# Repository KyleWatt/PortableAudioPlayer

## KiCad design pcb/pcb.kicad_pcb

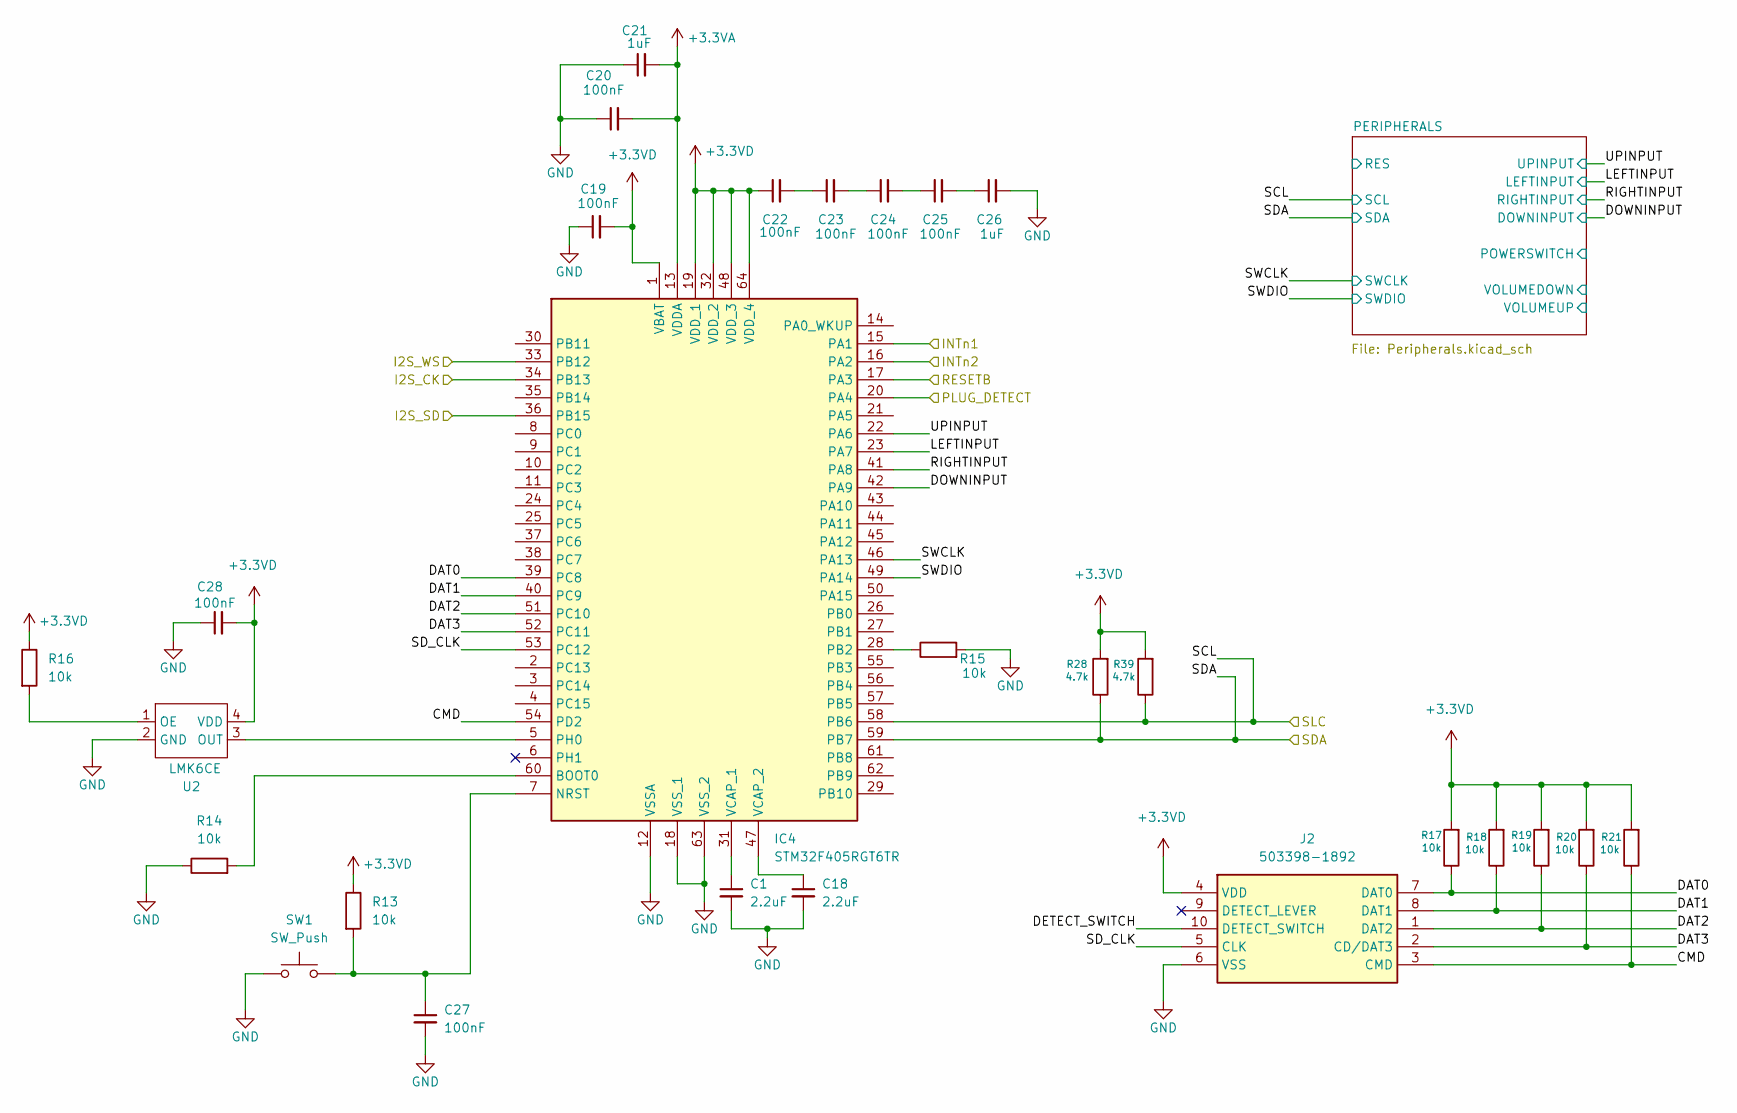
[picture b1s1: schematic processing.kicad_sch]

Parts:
C1, C18: 2.2uF; C_0805_2012Metric
C19, C20, C22, C23, C24, C25, C27, C28: 100nF; C_0805_2012Metric
C21, C26: 1uF; C_0805_2012Metric
IC4: STM32F405RGT6TR; QFP50P1200X1200X160-64N; Mouser Part Number 511-STM32F405RGT6TR
J2: 503398-1892; 5033981892; Mouser Part Number 538-503398-1892
R13, R14, R15, R16, R17, R18, R19, R20, R21: 10k; R_0805_2012Metric
R28, R39: 4.7k; R_0805_2012Metric
SW1: SW_Push; SW_Push_1P1T-MP_NO_Horizontal_Alps_SKRTLAE010
U2: LMK6CE; DLF0004A

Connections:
+3.3VA: C20.2, C21.2, IC4.13 (VDDA); also elsewhere on the board
+3.3VD: C19.2, C22.1, C28.2, IC4.1 (VBAT), IC4.19 (VDD_1), IC4.32 (VDD_2), IC4.48 (VDD_3), IC4.64 (VDD_4), J2.4 (VDD), R13.1, R16.1, R17.2, R18.2, R19.2, R20.2, R21.2, R28.2, R39.2, U2.4 (VDD); also elsewhere on the board
/AUDIO/I2S_CLK: IC4.34 (PB13); also elsewhere on the board
/AUDIO/I2S_SD: IC4.36 (PB15); also elsewhere on the board
/AUDIO/I2S_WS: IC4.33 (PB12); also elsewhere on the board
/AUDIO/PLUG_DETECT: IC4.20 (PA4); also elsewhere on the board
/AUDIO/RESETB: IC4.17 (PA3); also elsewhere on the board
/POWER/INTn1: IC4.15 (PA1); also elsewhere on the board
/POWER/INTn2: IC4.16 (PA2); also elsewhere on the board
/PROCESSING/CMD: IC4.54 (PD2), J2.3 (CMD), R21.1
/PROCESSING/DAT0: IC4.39 (PC8), J2.7 (DAT0), R17.1
/PROCESSING/DAT1: IC4.40 (PC9), J2.8 (DAT1), R18.1
/PROCESSING/DAT2: IC4.51 (PC10), J2.1 (DAT2), R19.1
/PROCESSING/DAT3: IC4.52 (PC11), J2.2 (CD/DAT3), R20.1
/PROCESSING/DETECT_SWITCH: J2.10 (DETECT_SWITCH)
/PROCESSING/DOWNINPUT: IC4.42 (PA9); also elsewhere on the board
/PROCESSING/LEFTINPUT: IC4.23 (PA7); also elsewhere on the board
/PROCESSING/RIGHTINPUT: IC4.41 (PA8); also elsewhere on the board
/PROCESSING/SCL: IC4.58 (PB6), R39.1; also elsewhere on the board
/PROCESSING/SDA: IC4.59 (PB7), R28.1; also elsewhere on the board
/PROCESSING/SD_CLK: IC4.53 (PC12), J2.5 (CLK)
/PROCESSING/SWCLK: IC4.46 (PA13); also elsewhere on the board
/PROCESSING/SWDIO: IC4.49 (PA14); also elsewhere on the board
/PROCESSING/UPINPUT: IC4.22 (PA6); also elsewhere on the board
GND: C1.2, C18.2, C19.1, C20.1, C21.1, C26.2, C27.2, C28.1, IC4.12 (VSSA), IC4.18 (VSS_1), IC4.63 (VSS_2), J2.6 (VSS), R14.1, R15.2, SW1.1, U2.2 (GND); also elsewhere on the board
unnamed: C22.2, C23.1
unnamed: C23.2, C24.1
unnamed: C24.2, C25.1
unnamed: C25.2, C26.1
unnamed: IC4.60 (BOOT0), R14.2
unnamed: C27.1, IC4.7 (NRST), R13.2, SW1.2
unnamed: IC4.28 (PB2), R15.1
unnamed: IC4.5 (PH0), U2.3 (OUT)
unnamed: C1.1, IC4.31 (VCAP_1)
unnamed: C18.1, IC4.47 (VCAP_2)
unnamed: R16.2, U2.1 (OE)

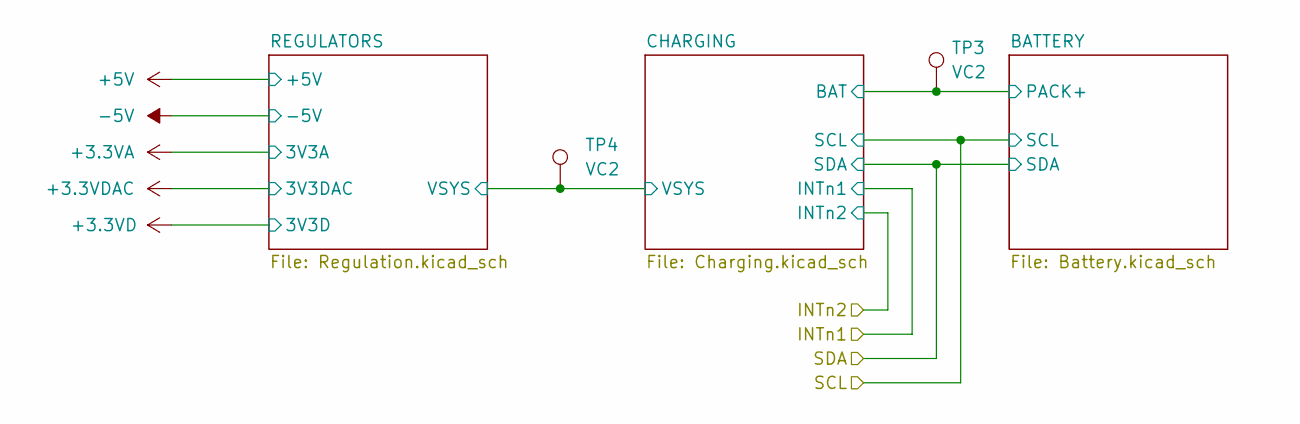
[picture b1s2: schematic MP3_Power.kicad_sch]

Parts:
TP3, TP4: VC2; TestPoint_Pad_3.0x3.0mm

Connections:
/POWER/BATTERY/PACK+: TP3.1; also elsewhere on the board
/POWER/CHARGING/VSYS: TP4.1; also elsewhere on the board

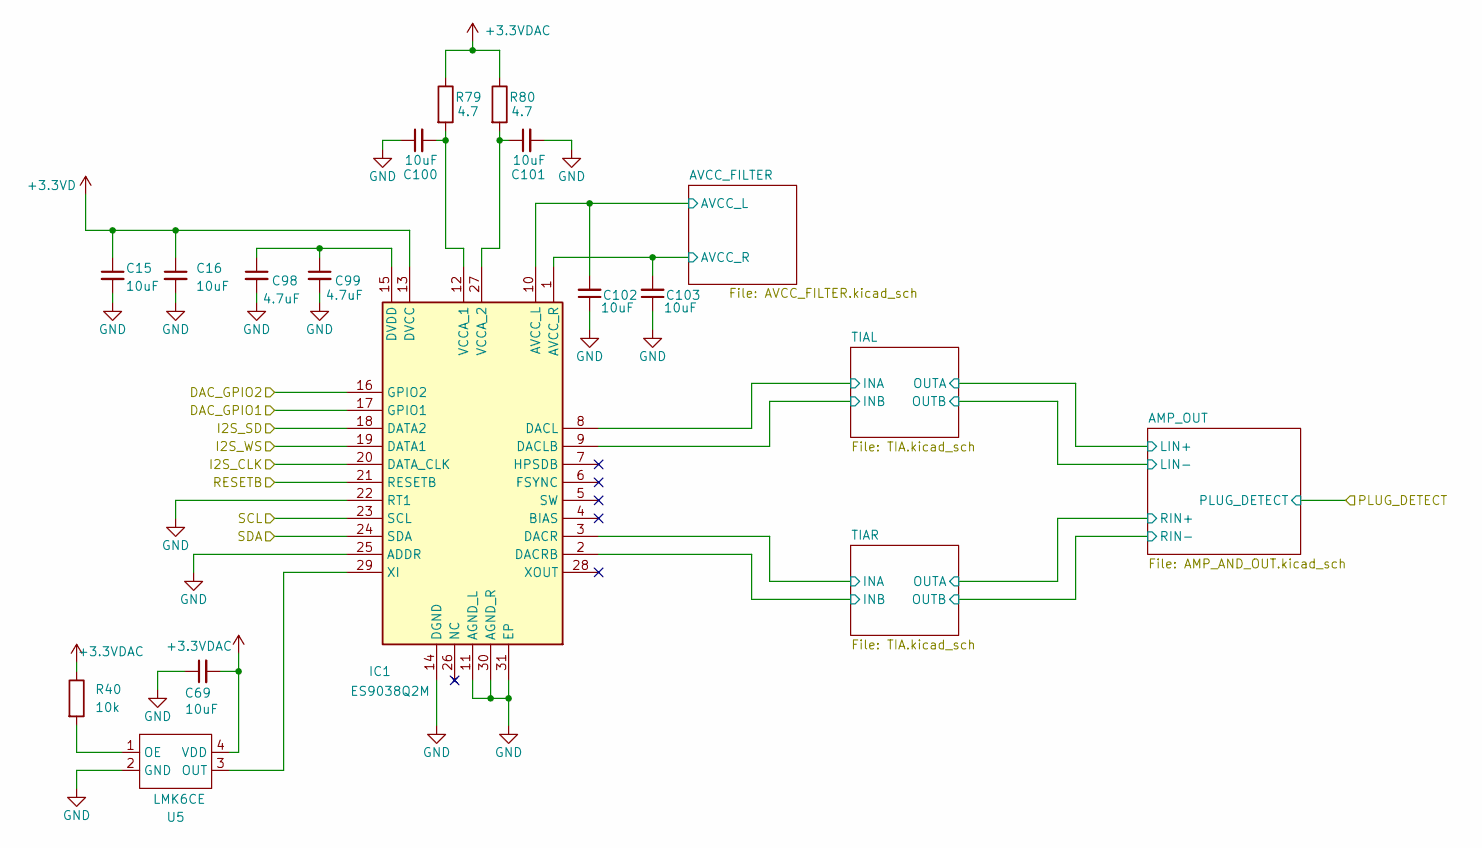
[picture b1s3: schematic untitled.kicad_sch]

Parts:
C15, C16, C69, C100, C101, C102, C103: 10uF; C_0805_2012Metric
C98, C99: 4.7uF; C_0805_2012Metric
IC1: ES9038Q2M; QFN40P300X500X80-31N-D; Mouser Part Number 460-ES9038Q2M
R40: 10k; R_0805_2012Metric
R79, R80: 4.7; R_0805_2012Metric
U5: LMK6CE; DLF0004A

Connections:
+3.3VD: C15.1, C16.1, IC1.13 (DVCC); also elsewhere on the board
+3.3VDAC: C69.2, R40.1, R79.1, R80.1, U5.4 (VDD); also elsewhere on the board
/AUDIO/AVCC_FILTER/AVCC_L: C102.2, IC1.10 (AVCC_L); also elsewhere on the board
/AUDIO/AVCC_FILTER/AVCC_R: C103.2, IC1.1 (AVCC_R); also elsewhere on the board
/AUDIO/DAC_GPIO1: IC1.17 (GPIO1)
/AUDIO/DAC_GPIO2: IC1.16 (GPIO2)
/AUDIO/I2S_CLK: IC1.20 (DATA_CLK); also elsewhere on the board
/AUDIO/I2S_SD: IC1.18 (DATA2); also elsewhere on the board
/AUDIO/I2S_WS: IC1.19 (DATA1); also elsewhere on the board
/AUDIO/RESETB: IC1.21 (RESETB); also elsewhere on the board
/AUDIO/TIAL/INA: IC1.8 (DACL); also elsewhere on the board
/AUDIO/TIAL/INB: IC1.9 (DACLB); also elsewhere on the board
/AUDIO/TIAR/INA: IC1.3 (DACR); also elsewhere on the board
/AUDIO/TIAR/INB: IC1.2 (DACRB); also elsewhere on the board
/PROCESSING/SCL: IC1.23 (SCL); also elsewhere on the board
/PROCESSING/SDA: IC1.24 (SDA); also elsewhere on the board
GND: C15.2, C16.2, C69.1, C98.2, C99.2, C100.1, C101.2, C102.1, C103.1, IC1.11 (AGND_L), IC1.14 (DGND), IC1.22 (RT1), IC1.25 (ADDR), IC1.30 (AGND_R), IC1.31 (EP), U5.2 (GND); also elsewhere on the board
unnamed: C98.1, C99.1, IC1.15 (DVDD)
unnamed: C100.2, IC1.12 (VCCA_1), R79.2
unnamed: C101.1, IC1.27 (VCCA_2), R80.2
unnamed: IC1.29 (XI), U5.3 (OUT)
unnamed: R40.2, U5.1 (OE)

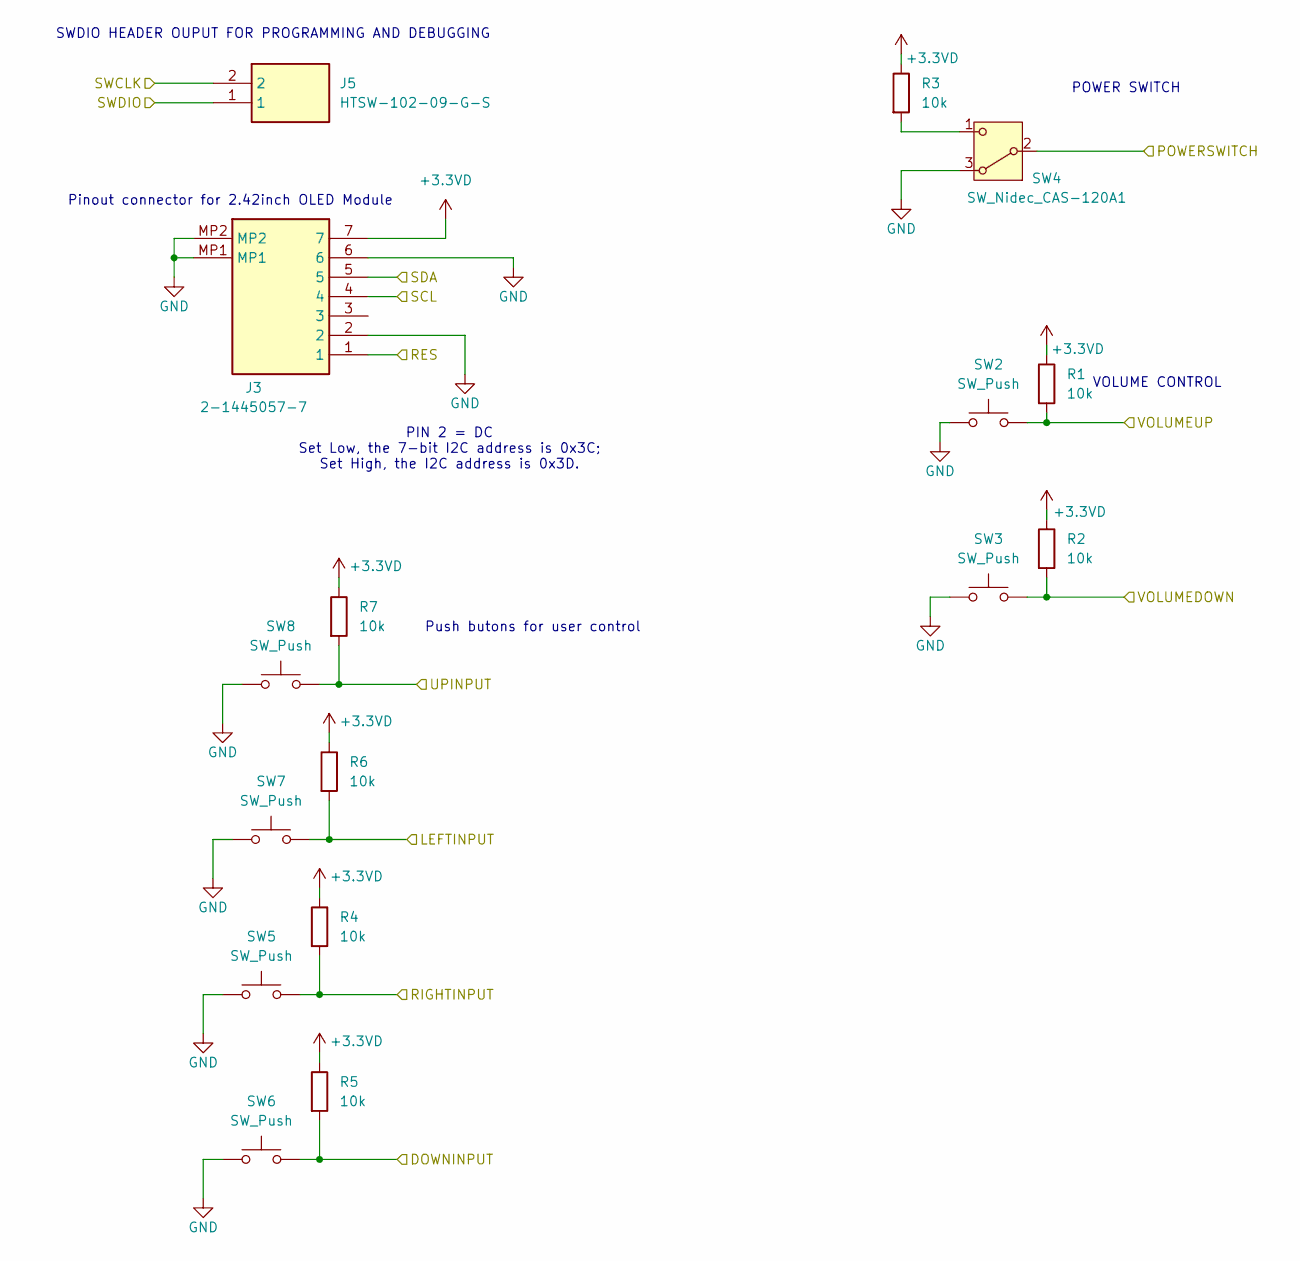
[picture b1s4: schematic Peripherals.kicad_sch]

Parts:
J3: 2-1445057-7; 214450577; Mouser Part Number 571-2-1445057-7
J5: HTSW-102-09-G-S; HTSW10209GS; Mouser Part Number 200-HTSW10209GS
R1, R2, R3, R4, R5, R6, R7: 10k; R_0805_2012Metric
SW2, SW3, SW5, SW6, SW7, SW8: SW_Push; SW_Push_1P1T-MP_NO_Horizontal_Alps_SKRTLAE010
SW4: SW_Nidec_CAS-120A1; Nidec_Copal_CAS-120A

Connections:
+3.3VD: J3.7, R1.1, R2.1, R3.1, R4.1, R5.1, R6.1, R7.1; also elsewhere on the board
/PROCESSING/DOWNINPUT: R5.2, SW6.2; also elsewhere on the board
/PROCESSING/LEFTINPUT: R6.2, SW7.2; also elsewhere on the board
/PROCESSING/PERIPHERALS/POWERSWITCH: SW4.2 (B)
/PROCESSING/PERIPHERALS/RES: J3.1
/PROCESSING/PERIPHERALS/VOLUMEDOWN: R2.2, SW3.2
/PROCESSING/PERIPHERALS/VOLUMEUP: R1.2, SW2.2
/PROCESSING/RIGHTINPUT: R4.2, SW5.2; also elsewhere on the board
/PROCESSING/SCL: J3.4; also elsewhere on the board
/PROCESSING/SDA: J3.5; also elsewhere on the board
/PROCESSING/SWCLK: J5.2; also elsewhere on the board
/PROCESSING/SWDIO: J5.1; also elsewhere on the board
/PROCESSING/UPINPUT: R7.2, SW8.2; also elsewhere on the board
GND: J3.2, J3.6, J3.MP1, J3.MP2, SW2.1, SW3.1, SW4.3 (A), SW5.1, SW6.1, SW7.1, SW8.1; also elsewhere on the board
unnamed: R3.2, SW4.1 (C)

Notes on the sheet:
PIN 2 = DC Set Low, the 7-bit I2C address is 0x3C; Set High, the I2C address is 0x3D.
Pinout connector for 2.42inch OLED Module
SWDIO HEADER OUPUT FOR PROGRAMMING AND DEBUGGING
Push butons for user control
POWER SWITCH
VOLUME CONTROL

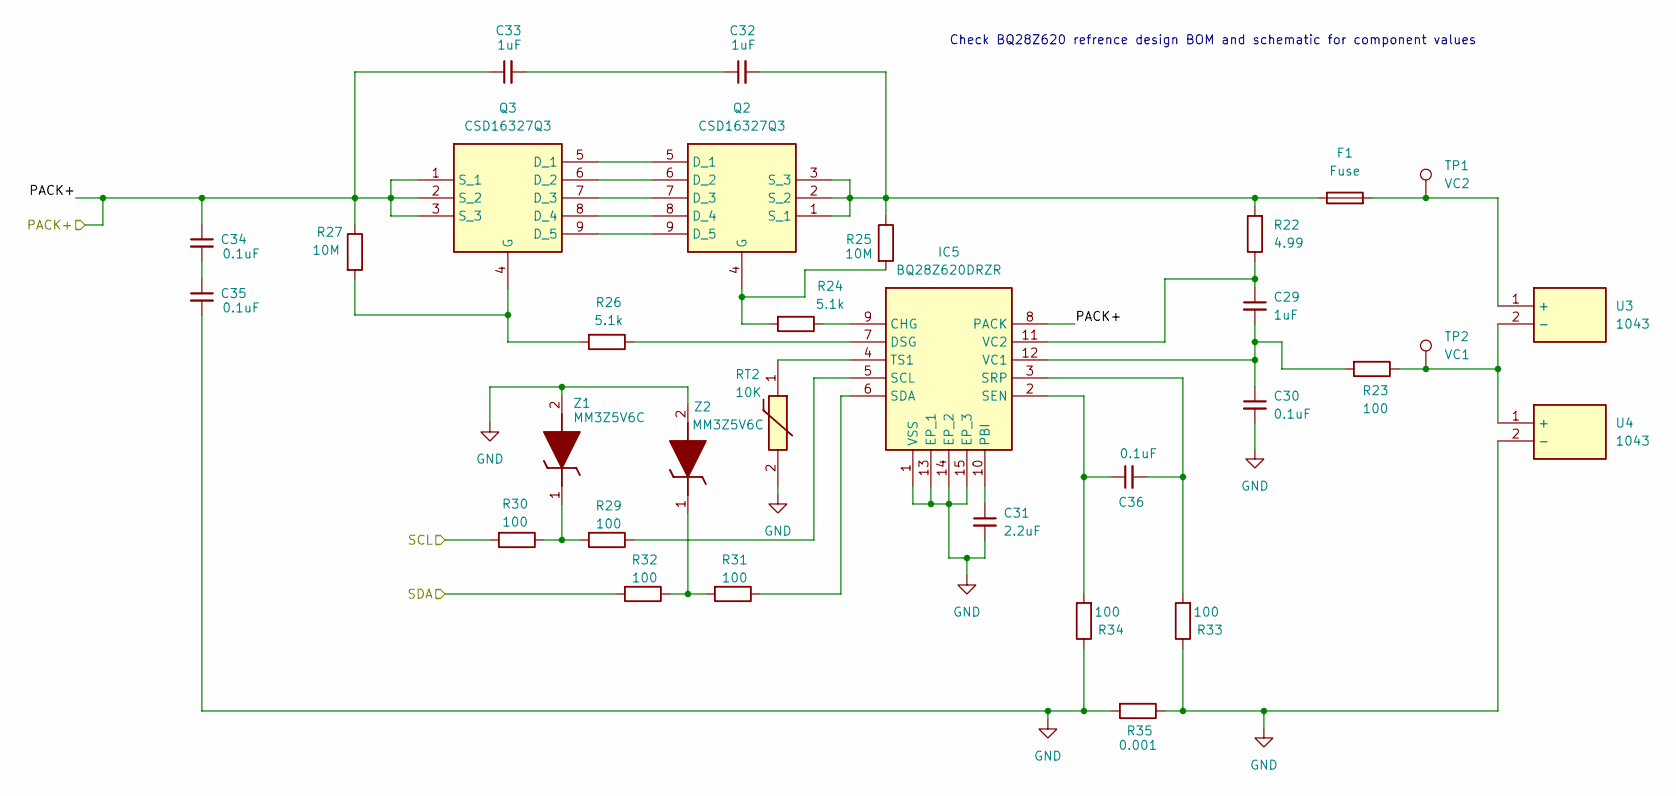
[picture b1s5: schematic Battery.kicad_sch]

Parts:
C29, C32, C33: 1uF; C_0805_2012Metric
C30, C34, C35, C36: 0.1uF; C_0805_2012Metric
C31: 2.2uF; C_0805_2012Metric
F1: Fuse; Fuse_0805_2012Metric
IC5: BQ28Z620DRZR; BQ28Z610DRZT; Mouser Part Number 595-BQ28Z620DRZR
Q2, Q3: CSD16327Q3; Mouser Part Number 595-CSD16327Q3
R22: 4.99; R_0805_2012Metric
R23, R29, R30, R31, R32, R33, R34: 100; R_0805_2012Metric
R24, R26: 5.1k; R_0805_2012Metric
R25, R27: 10M; R_0805_2012Metric
R35: 0.001; R_0805_2012Metric
RT2: 10K; 103AT2; Mouser Part Number 954-103AT-2
TP1: VC2; TestPoint_Pad_3.0x3.0mm
TP2: VC1; TestPoint_Pad_3.0x3.0mm
U3, U4: 1043; 1049; Mouser Part Number 534-1043
Z1, Z2: MM3Z5V6C; SODFL2513X100N; Mouser Part Number 512-MM3Z5V6C

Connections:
/POWER/BATTERY/PACK+: C33.1, C34.1, IC5.8 (PACK), Q3.1 (S_1), Q3.2 (S_2), Q3.3 (S_3), R27.1; also elsewhere on the board
/PROCESSING/SCL: R30.2; also elsewhere on the board
/PROCESSING/SDA: R32.2; also elsewhere on the board
GND: C30.2, C31.2, C35.2, IC5.1 (VSS), IC5.13 (EP_1), IC5.14 (EP_2), IC5.15 (EP_3), R33.1, R34.1, R35.1, R35.2, RT2.2, U4.2 (-), Z1.2 (A), Z2.2 (A); also elsewhere on the board
unnamed: C32.1, C33.2
unnamed: C34.2, C35.1
unnamed: IC5.9 (CHG), R24.1
unnamed: IC5.7 (DSG), R26.1
unnamed: C31.1, IC5.10 (PBI)
unnamed: IC5.5 (SCL), R29.1
unnamed: IC5.6 (SDA), R31.1
unnamed: C36.1, IC5.2 (SEN), R34.2
unnamed: C36.2, IC5.3 (SRP), R33.2
unnamed 85: IC5.4 (TS1), RT2.1; also elsewhere on the board
unnamed: C29.2, C30.1, IC5.12 (VC1), R23.2
unnamed: C29.1, IC5.11 (VC2), R22.1
unnamed: Q2.5 (D_1), Q3.5 (D_1)
unnamed: Q2.6 (D_2), Q3.6 (D_2)
unnamed: Q2.7 (D_3), Q3.7 (D_3)
unnamed: Q2.8 (D_4), Q3.8 (D_4)
unnamed: Q2.9 (D_5), Q3.9 (D_5)
unnamed: Q2.4 (G), R24.2, R25.2
unnamed: C32.2, F1.1, Q2.1 (S_1), Q2.2 (S_2), Q2.3 (S_3), R22.2, R25.1
unnamed: Q3.4 (G), R26.2, R27.2
unnamed: F1.2, TP1.1, U3.1 (+)
unnamed: R23.1, TP2.1, U3.2 (-), U4.1 (+)
unnamed: R29.2, R30.1, Z1.1 (K)
unnamed: R31.2, R32.1, Z2.1 (K)

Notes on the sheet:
Check BQ28Z620 refrence design BOM and schematic for component values

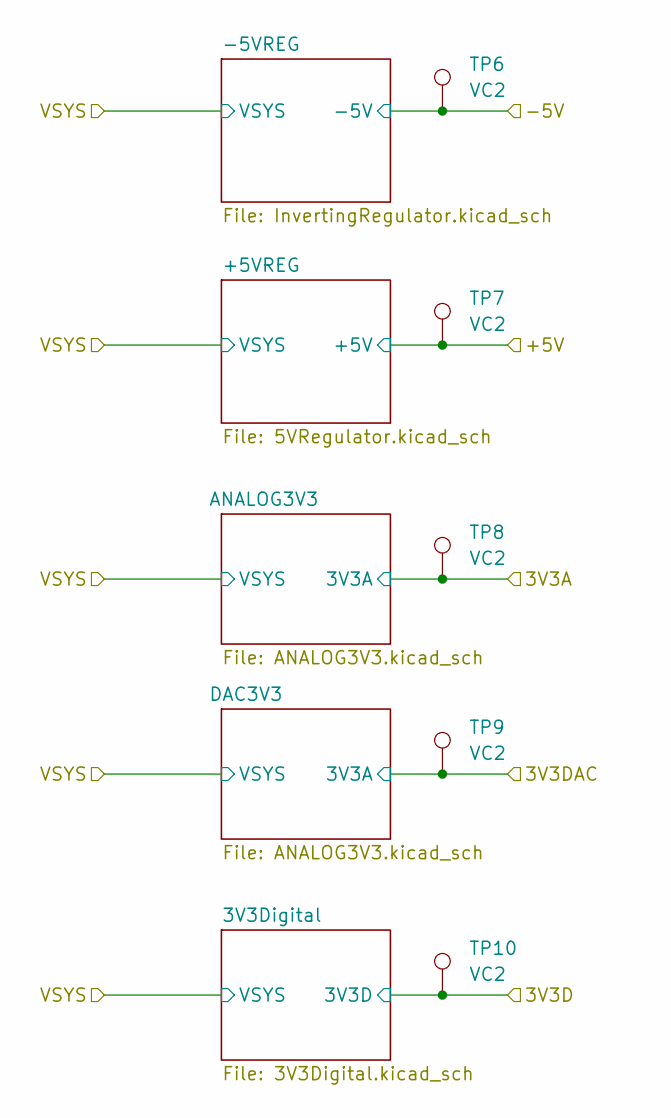
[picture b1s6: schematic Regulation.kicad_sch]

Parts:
TP6, TP7, TP8, TP9, TP10: VC2; TestPoint_Pad_3.0x3.0mm

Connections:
+3.3VA: TP8.1; also elsewhere on the board
+3.3VD: TP10.1; also elsewhere on the board
+3.3VDAC: TP9.1; also elsewhere on the board
+5V: TP7.1; also elsewhere on the board
-5V: TP6.1; also elsewhere on the board

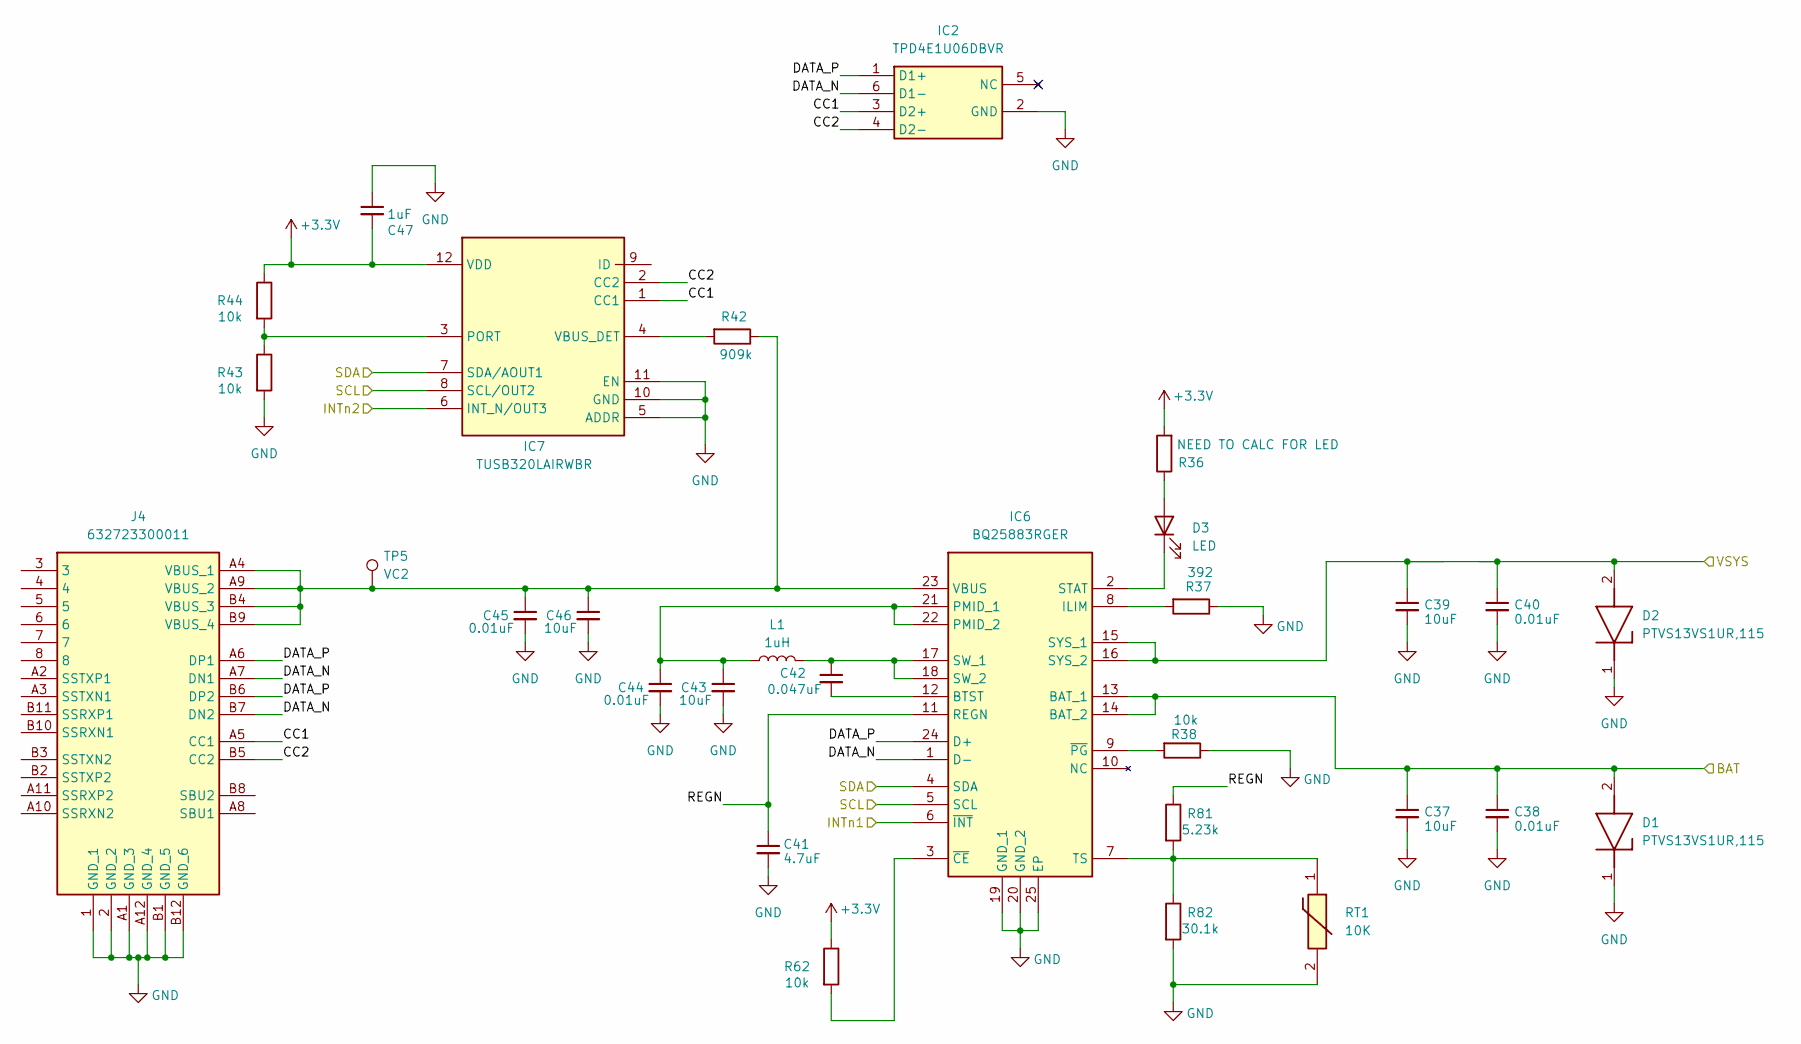
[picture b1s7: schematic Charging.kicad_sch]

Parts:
C37, C39, C43, C46: 10uF; C_0805_2012Metric
C38, C40, C44, C45: 0.01uF; C_0805_2012Metric
C41: 4.7uF; C_0805_2012Metric
C42: 0.047uF; C_0805_2012Metric
C47: 1uF; C_0805_2012Metric
D1, D2: PTVS13VS1UR,115; SOD123W; Mouser Part Number 771-PTVS13VS1UR115
D3: LED; LED_0805_2012Metric
IC2: TPD4E1U06DBVR; SOT95P280X145-6N; Mouser Part Number 595-TPD4E1U06DBVR
IC6: BQ25883RGER; QFN50P400X400X100-25N-D; Mouser Part Number 595-BQ25883RGER
IC7: TUSB320LAIRWBR; RWB0012A; Mouser Part Number 595-TUSB320LAIRWBR
J4: 632723300011; Mouser Part Number 710-632723300011
L1: 1uH; L_0805_2012Metric
R36: NEED TO CALC FOR LED; R_0805_2012Metric
R37: 392; R_0805_2012Metric
R38, R43, R44, R62: 10k; R_0805_2012Metric
R42: 909k; R_0805_2012Metric
R81: 5.23k; R_0805_2012Metric
R82: 30.1k; R_0805_2012Metric
RT1: 10K; 103AT2; Mouser Part Number 954-103AT-2
TP5: VC2; TestPoint_Pad_3.0x3.0mm

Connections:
+3.3V: C47.2, IC7.12 (VDD), R36.2, R44.1, R62.1
/POWER/BATTERY/PACK+: C37.1, C38.1, D1.2 (A), IC6.13 (BAT_1), IC6.14 (BAT_2); also elsewhere on the board
/POWER/CHARGING/CC1: IC2.3 (D2+), IC7.1 (CC1), J4.A5 (CC1)
/POWER/CHARGING/CC2: IC2.4 (D2-), IC7.2 (CC2), J4.B5 (CC2)
/POWER/CHARGING/DATA_N: IC2.6 (D1-), IC6.1 (D-), J4.A7 (DN1), J4.B7 (DN2)
/POWER/CHARGING/DATA_P: IC2.1 (D1+), IC6.24 (D+), J4.A6 (DP1), J4.B6 (DP2)
/POWER/CHARGING/REGN: C41.1, IC6.11 (REGN), R81.1
/POWER/CHARGING/VSYS: C39.1, C40.1, D2.2 (A), IC6.15 (SYS_1), IC6.16 (SYS_2); also elsewhere on the board
/POWER/INTn1: IC6.6 (~INT); also elsewhere on the board
/POWER/INTn2: IC7.6 (INT_N/OUT3); also elsewhere on the board
/PROCESSING/SCL: IC6.5 (SCL), IC7.8 (SCL/OUT2); also elsewhere on the board
/PROCESSING/SDA: IC6.4 (SDA), IC7.7 (SDA/AOUT1); also elsewhere on the board
GND: C37.2, C38.2, C39.2, C40.2, C41.2, C43.2, C44.2, C45.2, C46.2, C47.1, D1.1 (K), D2.1 (K), IC2.2 (GND), IC6.19 (GND_1), IC6.20 (GND_2), IC6.25 (EP), IC7.5 (ADDR), IC7.10 (GND), IC7.11 (EN), J4.1 (GND_1), J4.2 (GND_2), J4.A1 (GND_3), J4.A12 (GND_4), J4.B1 (GND_5), J4.B12 (GND_6), R37.1, R38.1, R43.2, R82.2, RT1.2; also elsewhere on the board
unnamed: D3.2 (A), R36.1
unnamed: D3.1 (K), IC6.2 (STAT)
unnamed: C42.2, IC6.12 (BTST)
unnamed: IC6.8 (ILIM), R37.2
unnamed: C43.1, C44.1, IC6.21 (PMID_1), IC6.22 (PMID_2), L1.1
unnamed: C42.1, IC6.17 (SW_1), IC6.18 (SW_2), L1.2
unnamed: IC6.7 (TS), R81.2, R82.1, RT1.1
unnamed: C45.1, C46.1, IC6.23 (VBUS), J4.A4 (VBUS_1), J4.A9 (VBUS_2), J4.B4 (VBUS_3), J4.B9 (VBUS_4), R42.1, TP5.1
unnamed: IC6.3 (~CE), R62.2
unnamed: IC6.9 (~PG), R38.2
unnamed: IC7.3 (PORT), R43.1, R44.2
unnamed: IC7.4 (VBUS_DET), R42.2

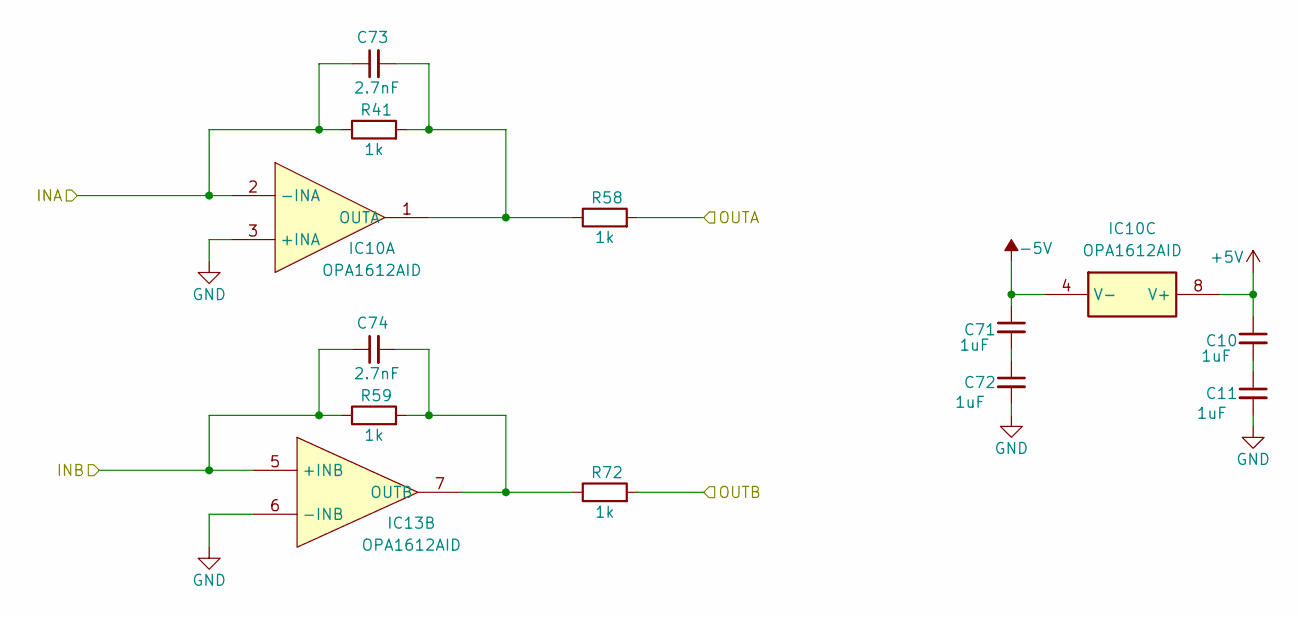
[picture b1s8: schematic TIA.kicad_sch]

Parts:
C10, C11, C71, C72: 1uF; C_0805_2012Metric
C73, C74: 2.7nF; C_0805_2012Metric
IC10, IC13: OPA1612AID; SOIC127P600X175-8N; Mouser Part Number 595-OPA1612AID
R41, R58, R59, R72: 1k; R_0805_2012Metric

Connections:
+5V: C10.1, IC10.8 (V+); also elsewhere on the board
-5V: C71.1, IC10.4 (V-); also elsewhere on the board
/AUDIO/AMP_OUT/LIN+: R58.2; also elsewhere on the board
/AUDIO/AMP_OUT/LIN-: R72.2; also elsewhere on the board
/AUDIO/TIAL/INA: C73.1, IC10.2 (-INA), R41.1; also elsewhere on the board
/AUDIO/TIAL/INB: C74.1, IC13.5 (+INB), R59.1; also elsewhere on the board
GND: C11.2, C72.2, IC10.3 (+INA), IC13.6 (-INB); also elsewhere on the board
unnamed: C10.2, C11.1
unnamed: C71.2, C72.1
unnamed: C73.2, IC10.1 (OUTA), R41.2, R58.1
unnamed: C74.2, IC13.7 (OUTB), R59.2, R72.1

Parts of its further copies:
C75, C76: 2.7nF; C_0805_2012Metric
C77, C78, C79, C80: 1uF; C_0805_2012Metric
IC11, IC14: OPA1612AID; SOIC127P600X175-8N; Mouser Part Number 595-OPA1612AID
R61, R63, R65, R73: 1k; R_0805_2012Metric

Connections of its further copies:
+5V: C77.1, IC11.8 (V+); also elsewhere on the board
-5V: C79.1, IC11.4 (V-); also elsewhere on the board
/AUDIO/AMP_OUT/RIN+: R65.2; also elsewhere on the board
/AUDIO/AMP_OUT/RIN-: R73.2; also elsewhere on the board
/AUDIO/TIAR/INA: C75.1, IC11.2 (-INA), R61.1; also elsewhere on the board
/AUDIO/TIAR/INB: C76.1, IC14.5 (+INB), R63.1; also elsewhere on the board
GND: C78.2, C80.2, IC11.3 (+INA), IC14.6 (-INB); also elsewhere on the board
unnamed: C77.2, C78.1
unnamed: C79.2, C80.1
unnamed: C75.2, IC11.1 (OUTA), R61.2, R65.1
unnamed: C76.2, IC14.7 (OUTB), R63.2, R73.1

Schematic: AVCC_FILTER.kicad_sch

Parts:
C14, C17, C87, C88: 1uF; C_0805_2012Metric
C70, C90: 47uF; C_0805_2012Metric
C85, C86, C89, C91: 10uF; C_0805_2012Metric
IC13, IC15: OPA1612AID; SOIC127P600X175-8N; Mouser Part Number 595-OPA1612AID
R60, R64: 22; R_0805_2012Metric

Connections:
+3.3VA: C85.2, C89.2, R60.1, R64.1; also elsewhere on the board
+5V: C14.1, IC13.8 (V+); also elsewhere on the board
-5V: C87.1, IC13.4 (V-); also elsewhere on the board
/AUDIO/AVCC_FILTER/AVCC_L: C91.2, IC15.7 (OUTB); also elsewhere on the board
/AUDIO/AVCC_FILTER/AVCC_R: C86.2, IC13.1 (OUTA); also elsewhere on the board
GND: C17.2, C70.1, C85.1, C86.1, C88.2, C89.1, C90.1, C91.1, IC13.3 (+INA), IC15.6 (-INB); also elsewhere on the board
unnamed: C14.2, C17.1
unnamed: C87.2, C88.1
unnamed: C70.2, IC13.2 (-INA), R60.2
unnamed: C90.2, IC15.5 (+INB), R64.2

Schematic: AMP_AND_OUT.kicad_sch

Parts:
C81, C82, C83, C84: 1uF; C_0805_2012Metric
IC3: TPA6120A2DWPR; SOIC127P1040X275-21N; Mouser Part Number 595-TPA6120A2DWPR
J1: SJ3-35083C-TR; SJ335083CTR; Mouser Part Number 179-SJ3-35083C-TR
R66, R67, R68, R69: 1k; R_0805_2012Metric
R70, R71: 39.2; R_0805_2012Metric

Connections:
+5V: C83.1, C84.1, IC3.3 (LVCC+), IC3.18 (RVCC+); also elsewhere on the board
-5V: C81.1, C82.1, IC3.1 (LVCC-), IC3.20 (RVCC-); also elsewhere on the board
/AUDIO/AMP_OUT/LIN+: IC3.4 (LIN+), R66.2; also elsewhere on the board
/AUDIO/AMP_OUT/LIN-: IC3.5 (LIN-), R69.1; also elsewhere on the board
/AUDIO/AMP_OUT/RIN+: IC3.17 (RIN+), R67.2; also elsewhere on the board
/AUDIO/AMP_OUT/RIN-: IC3.16 (RIN-), R68.1; also elsewhere on the board
/AUDIO/PLUG_DETECT: J1.4 (RING_SWITCH); also elsewhere on the board
GND: C81.2, C82.2, C83.2, C84.2, IC3.6 (NC_1), IC3.7 (NC_2), IC3.8 (NC_3), IC3.9 (NC_4), IC3.10 (NC_5), IC3.11 (NC_6), IC3.12 (NC_7), IC3.13 (NC_8), IC3.14 (NC_9), IC3.15 (NC_10), IC3.21 (EP), J1.1 (SLEEVE), R66.1, R67.1; also elsewhere on the board
unnamed: IC3.2 (LOUT), R69.2, R71.1
unnamed: IC3.19 (ROUT), R68.2, R70.1
unnamed: J1.5 (RING), R70.2
unnamed: J1.2 (TIP), R71.2

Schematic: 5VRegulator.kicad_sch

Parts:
C51: 10uF; C_0805_2012Metric
C52, C53, C54: 1uF; C_0805_2012Metric
C56: 22uF; C_0805_2012Metric
C57, C58: 4.7uF; C_0805_2012Metric
IC17: LT3045EMSE#PBF; SOP65P490X110-13N; Mouser Part Number 584-LT3045EMSE#PBF
R48: 52.3k; R_0805_2012Metric
R49: 750k; R_0805_2012Metric
R50: 49.9k; R_0805_2012Metric
R51: 200k; R_0805_2012Metric
R52: 249; R_0805_2012Metric

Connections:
+5V: IC17.11 (OUT_1), IC17.12 (OUT_2), R49.1; also elsewhere on the board
/POWER/CHARGING/VSYS: C51.1, C52.1, C53.1, C54.1, IC17.1 (IN_1), IC17.2 (IN_2), IC17.3 (IN_3), IC17.4 (EN/UV), R51.2; also elsewhere on the board
GND: C51.2, C52.2, C53.2, C54.2, C56.2, C57.1, C58.1, IC17.9 (GND_1), IC17.13 (GND_2), R48.1, R50.2, R52.2; also elsewhere on the board
unnamed: IC17.6 (ILIM), R52.1
unnamed: C57.2, IC17.10 (OUTS)
unnamed: IC17.5 (PG), R51.1
unnamed: C58.2, IC17.7 (PGFB), R49.2, R50.1
unnamed: C56.1, IC17.8 (SET), R48.2

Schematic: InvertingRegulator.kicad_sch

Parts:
C48, C49, C50: 4.7uF; C_0805_2012Metric
IC8: LM27761DSGT; SON50P200X200X80-9N; Mouser Part Number 595-LM27761DSGT
R45: 10k; R_0805_2012Metric
R46: 301k; R_0805_2012Metric
R47: 100k; R_0805_2012Metric

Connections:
-5V: IC8.4 (VOUT), R46.1; also elsewhere on the board
/POWER/CHARGING/VSYS: C50.1, IC8.1 (VIN), R45.2; also elsewhere on the board
GND: C48.1, C50.2, IC8.2 (GND), IC8.9 (EP), R47.2; also elsewhere on the board
unnamed: C49.1, IC8.8 (C1+)
unnamed: C49.2, IC8.7 (C1-)
unnamed: C48.2, IC8.3 (CPOUT)
unnamed: IC8.6 (EN), R45.1
unnamed: IC8.5 (VFB), R46.2, R47.1

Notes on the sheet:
VOUT =–1.22 V × (R1 + R2) / R2
R1/R2 = 3.098 => Vout = -5V

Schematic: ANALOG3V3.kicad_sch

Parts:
C55: 10uF; C_0805_2012Metric
C59, C60, C61: 1uF; C_0805_2012Metric
C62, C64: 4.7uF; C_0805_2012Metric
C63: 22uF; C_0805_2012Metric
IC12: LT3045EMSE#PBF; SOP65P490X110-13N; Mouser Part Number 584-LT3045EMSE#PBF
R53: 200k; R_0805_2012Metric
R54: 249; R_0805_2012Metric
R55: 31.6k; R_0805_2012Metric
R56: 453k; R_0805_2012Metric
R57: 49.9k; R_0805_2012Metric

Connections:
+3.3VA: IC12.11 (OUT_1), IC12.12 (OUT_2), R56.1; also elsewhere on the board
/POWER/CHARGING/VSYS: C55.1, C59.1, C60.1, C61.1, IC12.1 (IN_1), IC12.2 (IN_2), IC12.3 (IN_3), IC12.4 (EN/UV), R53.2; also elsewhere on the board
GND: C55.2, C59.2, C60.2, C61.2, C62.1, C63.2, C64.1, IC12.9 (GND_1), IC12.13 (GND_2), R54.2, R55.1, R57.2; also elsewhere on the board
unnamed: IC12.6 (ILIM), R54.1
unnamed: C62.2, IC12.10 (OUTS)
unnamed: IC12.5 (PG), R53.1
unnamed: C64.2, IC12.7 (PGFB), R56.2, R57.1
unnamed: C63.1, IC12.8 (SET), R55.2

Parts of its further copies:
C68: 10uF; C_0805_2012Metric
C92, C93, C94: 1uF; C_0805_2012Metric
C95, C97: 4.7uF; C_0805_2012Metric
C96: 22uF; C_0805_2012Metric
IC16: LT3045EMSE#PBF; SOP65P490X110-13N; Mouser Part Number 584-LT3045EMSE#PBF
R74: 200k; R_0805_2012Metric
R75: 249; R_0805_2012Metric
R76: 31.6k; R_0805_2012Metric
R77: 453k; R_0805_2012Metric
R78: 49.9k; R_0805_2012Metric

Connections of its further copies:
+3.3VDAC: IC16.11 (OUT_1), IC16.12 (OUT_2), R77.1; also elsewhere on the board
/POWER/CHARGING/VSYS: C68.1, C92.1, C93.1, C94.1, IC16.1 (IN_1), IC16.2 (IN_2), IC16.3 (IN_3), IC16.4 (EN/UV), R74.2; also elsewhere on the board
GND: C68.2, C92.2, C93.2, C94.2, C95.1, C96.2, C97.1, IC16.9 (GND_1), IC16.13 (GND_2), R75.2, R76.1, R78.2; also elsewhere on the board
unnamed: IC16.6 (ILIM), R75.1
unnamed: C95.2, IC16.10 (OUTS)
unnamed: IC16.5 (PG), R74.1
unnamed: C97.2, IC16.7 (PGFB), R77.2, R78.1
unnamed: C96.1, IC16.8 (SET), R76.2

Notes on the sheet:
During power-up, VOUT gradually ramps from 0V to 5V over 10-50ms, not instantly. The LT3045 uses the PGFB pin to detect whether it's starting up or already running. When VOUT is low (making PGFB < 300mV), the IC recognizes it's in start-up mode and pumps 2mA into the SET pin to quickly charge the l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
V_PGFB = VOUT × RPG1 / (RPG1 + RPG2) When V_PGFB < 0.3V FAST STARTUP ENGAGES When V_PGFB > 0.3V FAST STARTUP DISENGAGES VOUT(threshold) = 0.3V × (RPG1 + RPG2) / RPG1 VOUT(threshold) = 0.3V × (1 + RPG2/RPG1)
5V = 0.8V × (1 + R_SET/10kΩ) 5/0.8 = 1 + R_SET/10kΩ 6.25 = 1 + R_SET/10kΩ R_SET = 52.5kΩ

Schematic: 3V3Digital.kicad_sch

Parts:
C65, C66: 2.2uF; C_0805_2012Metric
C67: 1uF; C_0805_2012Metric
IC9: ADPL42002ARDZ-3.3-R7; SOIC127P600X175-9N; Manufacturer_Part_Number ADPL42002ARDZ-3.3-R7

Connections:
+3.3VD: C66.1, IC9.1 (VOUT_1), IC9.2 (VOUT_2), IC9.3 (SENSE); also elsewhere on the board
/POWER/CHARGING/VSYS: C65.1, IC9.5 (EN), IC9.7 (VIN_1), IC9.8 (VIN_2); also elsewhere on the board
GND: C65.2, C66.2, C67.2, IC9.4 (GND), IC9.9 (EP); also elsewhere on the board
unnamed: C67.1, IC9.6 (SS)

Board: 2 copper layers, 226 parts (0 on the bottom side), 137 nets, no tracks yet.

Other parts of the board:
TH1: 10k; R_0805_2012Metric

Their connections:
GND: TH1.2; also elsewhere on the board
unnamed 85: TH1.1; also elsewhere on the board

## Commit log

2025-10-28 Add files via upload
    Current Schematics for Protable HiFi
2025-12-16 Add KiCad project files
2025-12-16 Updated schematic pdf
2026-01-09 latest updates to schematic, changed to continuous ground
